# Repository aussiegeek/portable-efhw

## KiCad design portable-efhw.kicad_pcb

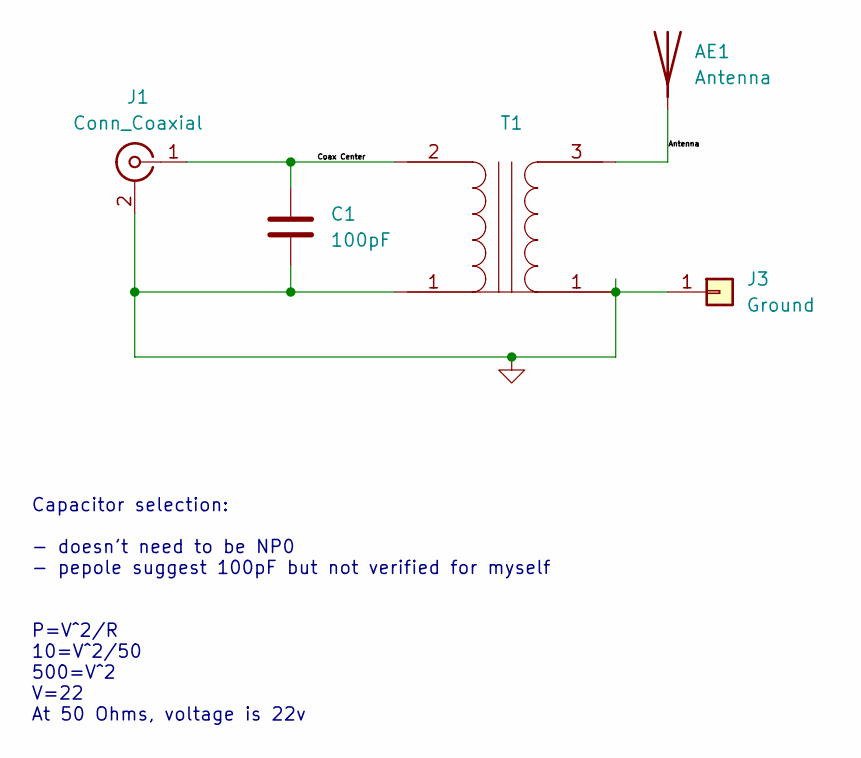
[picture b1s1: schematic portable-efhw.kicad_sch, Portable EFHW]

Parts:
AE1: Antenna; SolderWire-0.1sqmm_1x01_D0.4mm_OD1mm_Relief2x
C1: 100pF; C_0805_2012Metric_Pad1.18x1.45mm_HandSolder
J1: Conn_Coaxial; BNC_Amphenol_B6252HB-NPP3G-50_Horizontal; MPN CONBNC002; Mouser# 712-CONBNC002
J3: Ground; SolderWire-0.1sqmm_1x01_D0.4mm_OD1mm_Relief2x
T1: FerriteCore

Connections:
/Antenna: AE1.1 (A), T1.3
/Coax Center: C1.1, J1.1 (In), T1.2
GND: C1.2, J1.2 (Ext), J3.1, T1.1 (GND)

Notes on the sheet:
Capacitor selection: - doesn't need to be NP0 - pepole suggest 100pF but not verified for myself P=V^2/R 10=V^2/50 500=V^2 V=22 At 50 Ohms, voltage is 22v

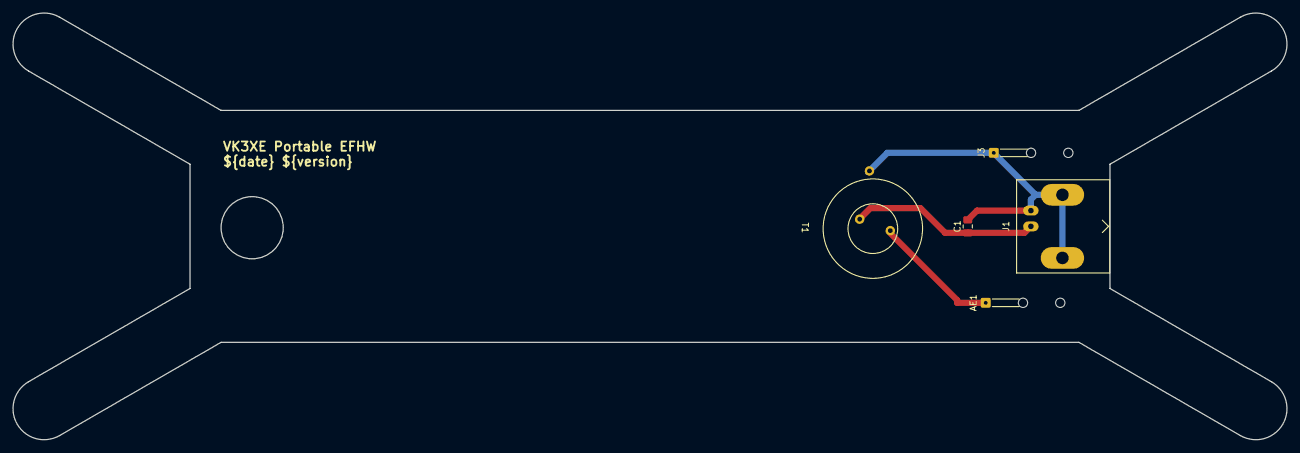
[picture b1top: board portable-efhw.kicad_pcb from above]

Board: 2 copper layers, 205.0 x 68.7 mm, 5 parts (0 on the bottom side), 3 nets.

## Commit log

2024-09-02 Make it so
